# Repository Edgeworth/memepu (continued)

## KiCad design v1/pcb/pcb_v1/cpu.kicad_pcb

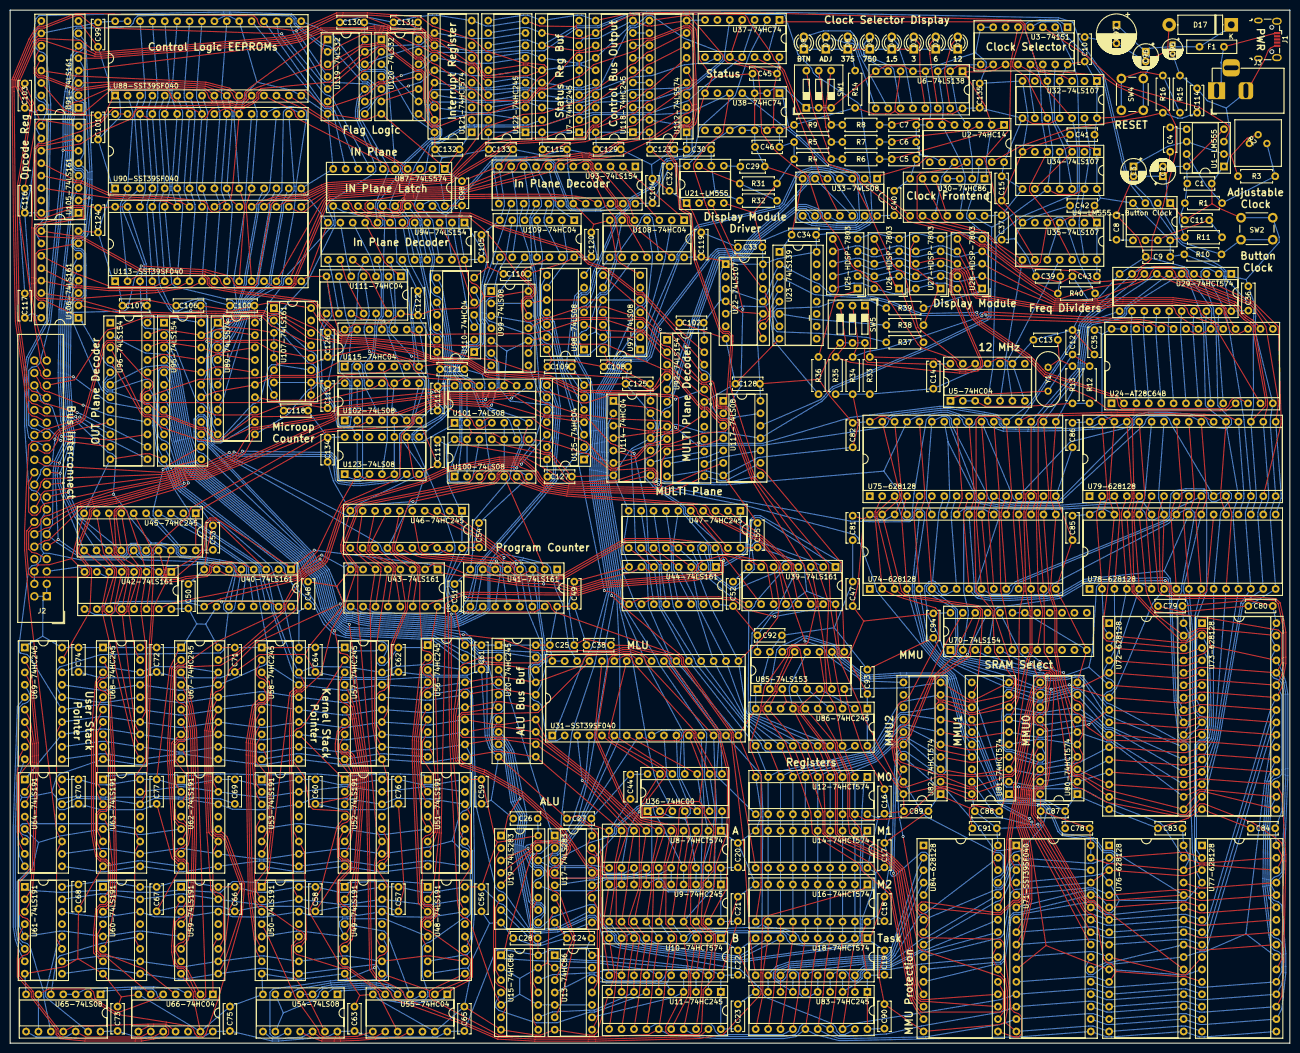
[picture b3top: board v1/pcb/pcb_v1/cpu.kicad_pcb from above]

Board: 2 copper layers, 262.0 x 211.5 mm, 299 parts (0 on the bottom side), 513 nets.

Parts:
C1, C5, C6, C7, C9, C10, C11, C14, C15, C16, C17, C18, C19, C20, C21, C22, C23, C24, C25, C26, C27, C28, C32, C33, C34, C35, C36, C37, C38, C40, C41, C42, C43, C44, C45, C46, C47, C48, C49, C50, C51, C52, C53, C54, C55, C56, C57, C58, C59, C60, C61, C62, C63, C64, C65, C66, C67, C68, C69, C70, C71, C72, C73, C74, C75, C76, C77, C78, C79, C80, C81, C82, C83, C84, C85, C86, C87, C88, C89, C90, C91, C92, C93, C94, C98, C99, C100, C101, C102, C103, C104, C105, C106, C107, C108, C109, C110, C111, C112, C113, C114, C115, C116, C117, C118, C119, C120, C121, C122, C123, C124, C125, C126, C127, C128, C129, C130, C131, C132, C133, C134, C135: 0.1uF; C_Disc_D6.0mm_W2.5mm_P5.00mm
C2, C3: 1uF; CP_Radial_D5.0mm_P2.00mm
C4, C8, C29: 10nF; C_Disc_D5.0mm_W2.5mm_P5.00mm
C12, C13: 27pF; C_Disc_D4.7mm_W2.5mm_P5.00mm
C30: 0.1nF; C_Disc_D6.0mm_W2.5mm_P5.00mm
C39: 1nF; C_Disc_D5.0mm_W2.5mm_P5.00mm
C95: 10uF; CP_Radial_D4.0mm_P2.00mm
C96: 100uF; CP_Radial_D5.0mm_P2.00mm
C97: 470uF; CP_Radial_D8.0mm_P3.80mm
D1, D2, D3, D4, D5, D6, D7, D8: LED; LED_D3.0mm
D17: 5.6V; D_5W_P12.70mm_Horizontal
F1: 0.65A; C_Disc_D10.0mm_W2.5mm_P5.00mm
J1: Conn_01x05; USB_Micro-B_Wuerth_629105150521
J2: Conn_02x20_Odd_Even; IDC-Header_2x20_P2.54mm_Vertical
J3: Conn_01x03; BarrelJack_Horizontal
R1, R13, R14: 1K; R_Axial_DIN0207_L6.3mm_D2.5mm_P7.62mm_Horizontal
R2: 1M; Akizuki-Denshi Potentiometer
R3, R31: 10K; R_Axial_DIN0207_L6.3mm_D2.5mm_P7.62mm_Horizontal
R4, R5, R9, R10, R15, R33, R34, R35: 100K; R_Axial_DIN0207_L6.3mm_D2.5mm_P7.62mm_Horizontal
R6, R7, R8, R11, R12, R16, R32, R40: 1M; R_Axial_DIN0207_L6.3mm_D2.5mm_P7.62mm_Horizontal
R36, R37, R38, R39: 100; R_Axial_DIN0207_L6.3mm_D2.5mm_P7.62mm_Horizontal
SW1: SW_DIP_x03 - Clock Source Select; SW_DIP_SPSTx03_Slide_9.78x9.8mm_W7.62mm_P2.54mm
SW2, SW4: SW_Push; SW_PUSH_6mm_H7.3mm
SW5: SW_DIP_x03; SW_DIP_SPSTx03_Slide_9.78x9.8mm_W7.62mm_P2.54mm
U1-LM555, U21-LM555: LM555; DIP-8_W7.62mm_Socket
U2-74HC14: 74HC14; DIP-14_W7.62mm_Socket
U3-74151: 74151; DIP-16_W7.62mm_Socket
U4-LM555 - Button Clock: LM555 - Button Clock; DIP-8_W7.62mm_Socket
U5-74HC04, U55-74HC04, U66-74HC04, U108-74HC04, U109-74HC04, U110-74HC04, U111-74HC04, U114-74HC04, U115-74HC04, U125-74HC04: 74HC04; DIP-14_W7.62mm_Socket
U6-74LS138: 74LS138; DIP-16_W7.62mm_Socket
U7-74HC245, U9-74HC245, U11-74HC245, U20-74HC245, U45-74HC245, U46-74HC245, U47-74HC245, U56-74HC245, U57-74HC245, U58-74HC245, U67-74HC245, U68-74HC245, U69-74HC245, U83-74HC245, U86-74HC245, U118-74HC245, U122-74HC245: 74HC245; DIP-20_W7.62mm_Socket
U8-74HCT574, U10-74HCT574, U12-74HCT574, U14-74HCT574, U16-74HCT574, U18-74HCT574, U29-74HCT574, U80-74HCT574, U81-74HCT574, U82-74HCT574, U121-74HCT574: 74HCT574; DIP-20_W7.62mm_Socket
U13-74HC86, U15-74HC86, U30-74HC86: 74HC86; DIP-14_W7.62mm_Socket
U17-74LS283, U19-74LS283: 74LS283; DIP-16_W7.62mm_Socket
U22-74LS107, U32-74LS107, U34-74LS107, U35-74LS107: 74LS107; DIP-14_W7.62mm_Socket
U23-74LS139: 74LS139; DIP-16_W7.62mm_Socket
U24-AT28C64B: AT28C64B; DIP-28_W15.24mm_Socket
U25-HDSP-7803, U26-HDSP-7803, U27-HDSP-7803, U28-HDSP-7803: HDSP-7803; HDSP-7801
U31-SST39SF040, U71-SST39SF040, U88-SST39SF040, U90-SST39SF040, U113-SST39SF040: SST39SF040; DIP-32_W15.24mm_Socket
U33-74LS08, U54-74LS08, U65-74LS08, U97-74LS08, U98-74LS08, U99-74LS08, U100-74LS08, U101-74LS08, U102-74LS08, U117-74LS08, U123-74LS08: 74LS08; DIP-14_W7.62mm_Socket
U36-74HC00: 74HC00; DIP-14_W7.62mm_Socket
U37-74HC74, U38-74HC74: 74HC74; DIP-14_W7.62mm_Socket
U39-74LS161, U40-74LS161, U41-74LS161, U42-74LS161, U43-74LS161, U44-74LS161, U91-74LS161, U105-74LS161, U106-74LS161, U107-74LS161: 74LS161; DIP-16_W7.62mm_Socket
U48-74LS191, U49-74LS191, U50-74LS191, U51-74LS191, U52-74LS191, U53-74LS191, U59-74LS191, U60-74LS191, U61-74LS191, U62-74LS191, U63-74LS191, U64-74LS191: 74LS191; DIP-16_W7.62mm_Socket
U70-74LS154, U92-74LS154, U93-74LS154, U94-74LS154, U95-74LS154, U96-74LS154: 74LS154; DIP-24_W7.62mm_Socket
U72-628128, U73-628128, U74-628128, U75-628128, U76-628128, U77-628128, U78-628128, U79-628128, U84-628128: 628128; DIP-32_W15.24mm_Socket
U85-74LS153: 74LS153; DIP-16_W7.62mm_Socket
U87-74LS574, U89-74LS574, U112-74LS574: 74LS574; DIP-20_W7.62mm_Socket
U119-74LS32, U120-74LS32: 74LS32; DIP-14_W7.62mm_Socket
Y1: 12MHz; Crystal_HC49-U_Vertical

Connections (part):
/A0: U8-74HCT574.19, U9-74HC245.2, U17-74LS283.5, U31-SST39SF040.12, U36-74HC00.1
/A1: U8-74HCT574.18, U9-74HC245.3, U17-74LS283.3, U31-SST39SF040.11, U36-74HC00.2
/A2: U8-74HCT574.17, U9-74HC245.4, U17-74LS283.14, U31-SST39SF040.10, U36-74HC00.4
/A3: U8-74HCT574.16, U9-74HC245.5, U17-74LS283.12, U31-SST39SF040.9, U36-74HC00.5
/A4: U8-74HCT574.15, U9-74HC245.6, U19-74LS283.5, U31-SST39SF040.8, U36-74HC00.9
/A5: U8-74HCT574.14, U9-74HC245.7, U19-74LS283.3, U31-SST39SF040.7, U36-74HC00.10
/A6: U8-74HCT574.13, U9-74HC245.8, U19-74LS283.14, U31-SST39SF040.6, U36-74HC00.12
/A7: U8-74HCT574.12, U9-74HC245.9, U19-74LS283.12, U31-SST39SF040.5, U36-74HC00.13
/ALU_FLAG_SET_CLK: U37-74HC74.3, U37-74HC74.11, U123-74LS08.8
/A_IN_CLK: U8-74HCT574.11, U97-74LS08.3
/B0: U10-74HCT574.19, U11-74HC245.2, U13-74HC86.1, U31-SST39SF040.27
/B1: U10-74HCT574.18, U11-74HC245.3, U13-74HC86.4, U31-SST39SF040.26
/B2: U10-74HCT574.17, U11-74HC245.4, U13-74HC86.9, U31-SST39SF040.23
/B3: U10-74HCT574.16, U11-74HC245.5, U13-74HC86.12, U31-SST39SF040.25
/B4: U10-74HCT574.15, U11-74HC245.6, U15-74HC86.1, U31-SST39SF040.4
/B5: U10-74HCT574.14, U11-74HC245.7, U15-74HC86.4, U31-SST39SF040.28
/B6: U10-74HCT574.13, U11-74HC245.8, U15-74HC86.9, U31-SST39SF040.29
/B7: U10-74HCT574.12, U11-74HC245.9, U15-74HC86.12, U31-SST39SF040.3
/BUS0: J2.9, U7-74HC245.18, U8-74HCT574.2, U9-74HC245.18, U10-74HCT574.2, U11-74HC245.18, U12-74HCT574.2, U12-74HCT574.19, U14-74HCT574.2, U14-74HCT574.19, U16-74HCT574.2, U16-74HCT574.19, U18-74HCT574.2, U20-74HC245.18, U29-74HCT574.2, U31-SST39SF040.13, U39-74LS161.3, U40-74LS161.3, U41-74LS161.3, U45-74HC245.18, U46-74HC245.18, U47-74HC245.18, U48-74LS191.15, U49-74LS191.15, U50-74LS191.15, U56-74HC245.18, U57-74HC245.18, U58-74HC245.18, U59-74LS191.15, U60-74LS191.15, U61-74LS191.15, U67-74HC245.18, U68-74HC245.18, U69-74HC245.18, U71-SST39SF040.13, U72-628128.13, U73-628128.13, U74-628128.13, U75-628128.13, U76-628128.13, U77-628128.13, U78-628128.13, U79-628128.13, U80-74HCT574.2, U81-74HCT574.2, U82-74HCT574.2, U83-74HC245.18, U86-74HC245.18, U91-74LS161.3, U105-74LS161.3, U118-74HC245.18, U122-74HC245.18
/BUS1: J2.11, U7-74HC245.17, U8-74HCT574.3, U9-74HC245.17, U10-74HCT574.3, U11-74HC245.17, U12-74HCT574.3, U12-74HCT574.18, U14-74HCT574.3, U14-74HCT574.18, U16-74HCT574.3, U16-74HCT574.18, U18-74HCT574.3, U20-74HC245.17, U29-74HCT574.3, U31-SST39SF040.14, U39-74LS161.4, U40-74LS161.4, U41-74LS161.4, U45-74HC245.17, U46-74HC245.17, U47-74HC245.17, U48-74LS191.1, U49-74LS191.1, U50-74LS191.1, U56-74HC245.17, U57-74HC245.17, U58-74HC245.17, U59-74LS191.1, U60-74LS191.1, U61-74LS191.1, U67-74HC245.17, U68-74HC245.17, U69-74HC245.17, U71-SST39SF040.14, U72-628128.14, U73-628128.14, U74-628128.14, U75-628128.14, U76-628128.14, U77-628128.14, U78-628128.14, U79-628128.14, U80-74HCT574.3, U81-74HCT574.3, U82-74HCT574.3, U83-74HC245.17, U86-74HC245.17, U91-74LS161.4, U105-74LS161.4, U118-74HC245.17, U122-74HC245.17
/BUS2: J2.13, U7-74HC245.16, U8-74HCT574.4, U9-74HC245.16, U10-74HCT574.4, U11-74HC245.16, U12-74HCT574.4, U12-74HCT574.17, U14-74HCT574.4, U14-74HCT574.17, U16-74HCT574.4, U16-74HCT574.17, U18-74HCT574.4, U20-74HC245.16, U29-74HCT574.4, U31-SST39SF040.15, U39-74LS161.5, U40-74LS161.5, U41-74LS161.5, U45-74HC245.16, U46-74HC245.16, U47-74HC245.16, U48-74LS191.10, U49-74LS191.10, U50-74LS191.10, U56-74HC245.16, U57-74HC245.16, U58-74HC245.16, U59-74LS191.10, U60-74LS191.10, U61-74LS191.10, U67-74HC245.16, U68-74HC245.16, U69-74HC245.16, U71-SST39SF040.15, U72-628128.15, U73-628128.15, U74-628128.15, U75-628128.15, U76-628128.15, U77-628128.15, U78-628128.15, U79-628128.15, U80-74HCT574.4, U81-74HCT574.4, U82-74HCT574.4, U83-74HC245.16, U86-74HC245.16, U91-74LS161.5, U105-74LS161.5, U118-74HC245.16, U122-74HC245.16
/BUS3: J2.15, U7-74HC245.15, U8-74HCT574.5, U9-74HC245.15, U10-74HCT574.5, U11-74HC245.15, U12-74HCT574.5, U12-74HCT574.16, U14-74HCT574.5, U14-74HCT574.16, U16-74HCT574.5, U16-74HCT574.16, U18-74HCT574.5, U20-74HC245.15, U29-74HCT574.5, U31-SST39SF040.17, U39-74LS161.6, U40-74LS161.6, U41-74LS161.6, U45-74HC245.15, U46-74HC245.15, U47-74HC245.15, U48-74LS191.9, U49-74LS191.9, U50-74LS191.9, U56-74HC245.15, U57-74HC245.15, U58-74HC245.15, U59-74LS191.9, U60-74LS191.9, U61-74LS191.9, U67-74HC245.15, U68-74HC245.15, U69-74HC245.15, U71-SST39SF040.17, U72-628128.17, U73-628128.17, U74-628128.17, U75-628128.17, U76-628128.17, U77-628128.17, U78-628128.17, U79-628128.17, U80-74HCT574.5, U81-74HCT574.5, U82-74HCT574.5, U83-74HC245.15, U86-74HC245.15, U91-74LS161.6, U105-74LS161.6, U118-74HC245.15, U122-74HC245.15
/BUS4: J2.17, U7-74HC245.14, U8-74HCT574.6, U9-74HC245.14, U10-74HCT574.6, U11-74HC245.14, U12-74HCT574.6, U12-74HCT574.15, U14-74HCT574.6, U14-74HCT574.15, U16-74HCT574.6, U16-74HCT574.15, U18-74HCT574.6, U20-74HC245.14, U29-74HCT574.6, U31-SST39SF040.18, U42-74LS161.3, U43-74LS161.3, U44-74LS161.3, U45-74HC245.14, U46-74HC245.14, U47-74HC245.14, U51-74LS191.15, U52-74LS191.15, U53-74LS191.15, U56-74HC245.14, U57-74HC245.14, U58-74HC245.14, U62-74LS191.15, U63-74LS191.15, U64-74LS191.15, U67-74HC245.14, U68-74HC245.14, U69-74HC245.14, U71-SST39SF040.18, U72-628128.18, U73-628128.18, U74-628128.18, U75-628128.18, U76-628128.18, U77-628128.18, U78-628128.18, U79-628128.18, U80-74HCT574.6, U81-74HCT574.6, U82-74HCT574.6, U83-74HC245.14, U86-74HC245.14, U106-74LS161.3, U118-74HC245.14, U122-74HC245.14
/BUS5: J2.19, U7-74HC245.13, U8-74HCT574.7, U9-74HC245.13, U10-74HCT574.7, U11-74HC245.13, U12-74HCT574.7, U12-74HCT574.14, U14-74HCT574.7, U14-74HCT574.14, U16-74HCT574.7, U16-74HCT574.14, U18-74HCT574.7, U20-74HC245.13, U29-74HCT574.7, U31-SST39SF040.19, U42-74LS161.4, U43-74LS161.4, U44-74LS161.4, U45-74HC245.13, U46-74HC245.13, U47-74HC245.13, U51-74LS191.1, U52-74LS191.1, U53-74LS191.1, U56-74HC245.13, U57-74HC245.13, U58-74HC245.13, U62-74LS191.1, U63-74LS191.1, U64-74LS191.1, U67-74HC245.13, U68-74HC245.13, U69-74HC245.13, U71-SST39SF040.19, U72-628128.19, U73-628128.19, U74-628128.19, U75-628128.19, U76-628128.19, U77-628128.19, U78-628128.19, U79-628128.19, U80-74HCT574.7, U81-74HCT574.7, U82-74HCT574.7, U83-74HC245.13, U86-74HC245.13, U106-74LS161.4, U118-74HC245.13, U122-74HC245.13
/BUS6: J2.21, U7-74HC245.12, U8-74HCT574.8, U9-74HC245.12, U10-74HCT574.8, U11-74HC245.12, U12-74HCT574.8, U12-74HCT574.13, U14-74HCT574.8, U14-74HCT574.13, U16-74HCT574.8, U16-74HCT574.13, U18-74HCT574.8, U20-74HC245.12, U29-74HCT574.8, U31-SST39SF040.20, U42-74LS161.5, U43-74LS161.5, U44-74LS161.5, U45-74HC245.12, U46-74HC245.12, U47-74HC245.12, U51-74LS191.10, U52-74LS191.10, U53-74LS191.10, U56-74HC245.12, U57-74HC245.12, U58-74HC245.12, U62-74LS191.10, U63-74LS191.10, U64-74LS191.10, U67-74HC245.12, U68-74HC245.12, U69-74HC245.12, U71-SST39SF040.20, U72-628128.20, U73-628128.20, U74-628128.20, U75-628128.20, U76-628128.20, U77-628128.20, U78-628128.20, U79-628128.20, U80-74HCT574.8, U81-74HCT574.8, U82-74HCT574.8, U83-74HC245.12, U86-74HC245.12, U106-74LS161.5, U118-74HC245.12, U122-74HC245.12
/BUS7: J2.23, U7-74HC245.11, U8-74HCT574.9, U9-74HC245.11, U10-74HCT574.9, U11-74HC245.11, U12-74HCT574.9, U12-74HCT574.12, U14-74HCT574.9, U14-74HCT574.12, U16-74HCT574.9, U16-74HCT574.12, U18-74HCT574.9, U20-74HC245.11, U29-74HCT574.9, U31-SST39SF040.21, U42-74LS161.6, U43-74LS161.6, U44-74LS161.6, U45-74HC245.11, U46-74HC245.11, U47-74HC245.11, U51-74LS191.9, U52-74LS191.9, U53-74LS191.9, U56-74HC245.11, U57-74HC245.11, U58-74HC245.11, U62-74LS191.9, U63-74LS191.9, U64-74LS191.9, U67-74HC245.11, U68-74HC245.11, U69-74HC245.11, U71-SST39SF040.21, U72-628128.21, U73-628128.21, U74-628128.21, U75-628128.21, U76-628128.21, U77-628128.21, U78-628128.21, U79-628128.21, U80-74HCT574.9, U81-74HCT574.9, U82-74HCT574.9, U83-74HC245.11, U86-74HC245.11, U106-74LS161.6, U118-74HC245.11, U122-74HC245.11
/B_IN_CLK: U10-74HCT574.11, U97-74LS08.6
/CARRY: U19-74LS283.9, U37-74HC74.2
/CLK: J2.5, U5-74HC04.13, U33-74LS08.3, U39-74LS161.2, U40-74LS161.2, U41-74LS161.2, U42-74LS161.2, U43-74LS161.2, U44-74LS161.2, U48-74LS191.14, U49-74LS191.14, U50-74LS191.14, U51-74LS191.14, U52-74LS191.14, U53-74LS191.14, U59-74LS191.14, U60-74LS191.14, U61-74LS191.14, U62-74LS191.14, U63-74LS191.14, U64-74LS191.14, U91-74LS161.2, U97-74LS08.2, U97-74LS08.5, U97-74LS08.10, U97-74LS08.13, U98-74LS08.2, U98-74LS08.5, U98-74LS08.10, U98-74LS08.13, U99-74LS08.2, U99-74LS08.5, U99-74LS08.10, U99-74LS08.13, U100-74LS08.2, U100-74LS08.5, U100-74LS08.10, U100-74LS08.13, U101-74LS08.2, U101-74LS08.5, U101-74LS08.10, U101-74LS08.13, U102-74LS08.2, U102-74LS08.5, U102-74LS08.10, U102-74LS08.13, U105-74LS161.2, U106-74LS161.2, U107-74LS161.2, U123-74LS08.2, U123-74LS08.5, U123-74LS08.10, U123-74LS08.13
/Clock/1.5MHZ_CLK: U3-74151.15, U34-74LS107.3, U34-74LS107.9
/Clock/3MHZ_CLK: U3-74151.14, U32-74LS107.5, U34-74LS107.12
/Clock/6MHZ_CLK: U3-74151.13, U32-74LS107.3, U32-74LS107.9
/Clock/12MHZ_CLK: U3-74151.12, U5-74HC04.4, U32-74LS107.12
/Clock/375KHZ_CLK: U3-74151.2, U35-74LS107.3
/Clock/750KHZ_CLK: U3-74151.1, U34-74LS107.5, U35-74LS107.12
/Clock/AC_TR: C3.1, R2.2, R3.2, U1-LM555.2, U1-LM555.6
/Clock/ADJ_CLK: U1-LM555.3, U3-74151.3
/Clock/BTN_CLK: U3-74151.4, U4-LM555 - Button Clock.3
/Clock/PRE_CLK: U3-74151.5, U33-74LS08.1, U35-74LS107.9
/Clock/SEL0: U2-74HC14.2, U3-74151.11, U6-74LS138.1, U30-74HC86.1
/Clock/SEL1: U2-74HC14.4, U3-74151.10, U6-74LS138.2, U30-74HC86.2
/Clock/SEL2: U2-74HC14.6, U3-74151.9, U6-74LS138.3, U30-74HC86.12
/Control Logic/ALU_FLAG_SET_NCLK: U114-74HC04.8, U123-74LS08.9
/Control Logic/A_IN_NCLK: U97-74LS08.1, U108-74HC04.2
/Control Logic/B_IN_NCLK: U97-74LS08.4, U108-74HC04.4
/Control Logic/CTRL0: U87-74LS574.2, U88-SST39SF040.13
/Control Logic/CTRL1: U87-74LS574.3, U88-SST39SF040.14
/Control Logic/CTRL2: U87-74LS574.4, U88-SST39SF040.15
/Control Logic/CTRL3: U87-74LS574.5, U88-SST39SF040.17
/Control Logic/CTRL4: U87-74LS574.6, U88-SST39SF040.18
/Control Logic/CTRL5: U87-74LS574.7, U88-SST39SF040.19
/Control Logic/CTRL6: U87-74LS574.8, U88-SST39SF040.20
/Control Logic/CTRL7: U87-74LS574.9, U88-SST39SF040.21
/Control Logic/CTRL8: U89-74LS574.2, U90-SST39SF040.13
/Control Logic/CTRL9: U89-74LS574.3, U90-SST39SF040.14
/Control Logic/CTRL10: U89-74LS574.4, U90-SST39SF040.15
/Control Logic/CTRL11: U89-74LS574.5, U90-SST39SF040.17
/Control Logic/CTRL12: U89-74LS574.6, U90-SST39SF040.18
/Control Logic/CTRL13: U89-74LS574.7, U90-SST39SF040.19
/Control Logic/CTRL14: U89-74LS574.8, U90-SST39SF040.20
/Control Logic/CTRL15: U89-74LS574.9, U90-SST39SF040.21
/Control Logic/CTRL16: U112-74LS574.2, U113-SST39SF040.13
/Control Logic/CTRL17: U112-74LS574.3, U113-SST39SF040.14
/Control Logic/CTRL18: U112-74LS574.4, U113-SST39SF040.15
/Control Logic/CTRL19: U112-74LS574.5, U113-SST39SF040.17
/Control Logic/CTRL20: U112-74LS574.6, U113-SST39SF040.18
/Control Logic/CTRL21: U112-74LS574.7, U113-SST39SF040.19
/Control Logic/CTRL22: U112-74LS574.8, U113-SST39SF040.20
/Control Logic/CTRL23: U112-74LS574.9, U113-SST39SF040.21
/Control Logic/CTRL_BUS1: U112-74LS574.18, U118-74HC245.3
/Control Logic/CTRL_BUS2: U112-74LS574.17, U118-74HC245.4
/Control Logic/CTRL_BUS3: U112-74LS574.16, U118-74HC245.5
/Control Logic/CTRL_BUS4: U112-74LS574.15, U118-74HC245.6
/Control Logic/CTRL_BUS5: U112-74LS574.14, U118-74HC245.7
/Control Logic/CTRL_BUS6: U112-74LS574.13, U118-74HC245.8
/Control Logic/CTRL_BUS7: U112-74LS574.12, U118-74HC245.9
/Control Logic/CTRL_IN0: U87-74LS574.19, U93-74LS154.23, U94-74LS154.23
/Control Logic/CTRL_IN1: U87-74LS574.18, U93-74LS154.22, U94-74LS154.22
/Control Logic/CTRL_IN2: U87-74LS574.17, U93-74LS154.21, U94-74LS154.21
/Control Logic/CTRL_IN3: U87-74LS574.16, U93-74LS154.20, U94-74LS154.20
/Control Logic/CTRL_IN4: U87-74LS574.15, U93-74LS154.18, U115-74HC04.11
/Control Logic/CTRL_MULTI0: U87-74LS574.14, U92-74LS154.23
/Control Logic/CTRL_MULTI1: U87-74LS574.13, U92-74LS154.22
/Control Logic/CTRL_MULTI2: U87-74LS574.12, U92-74LS154.21
/Control Logic/CTRL_MULTI3: U89-74LS574.14, U92-74LS154.20
/Control Logic/CTRL_OUT0: U89-74LS574.19, U95-74LS154.23, U96-74LS154.23
/Control Logic/CTRL_OUT1: U89-74LS574.18, U95-74LS154.22, U96-74LS154.22
/Control Logic/CTRL_OUT2: U89-74LS574.17, U95-74LS154.21, U96-74LS154.21
/Control Logic/CTRL_OUT3: U89-74LS574.16, U95-74LS154.20, U96-74LS154.20
/Control Logic/CTRL_OUT4: U89-74LS574.15, U95-74LS154.18, U115-74HC04.5
/Control Logic/DISP_IN_NCLK: U101-74LS08.1, U110-74HC04.10
/Control Logic/Flag Logic/INT_FLAG: U117-74LS08.1, U120-74LS32.8
/Control Logic/IN plane decoder/~S4: U94-74LS154.18, U115-74HC04.10
/Control Logic/INT0_IN_NCLK: U101-74LS08.9, U111-74HC04.2
/Control Logic/INT1_IN_NCLK: U101-74LS08.12, U111-74HC04.4
/Control Logic/INT2_IN_NCLK: U102-74LS08.1, U111-74HC04.6
/Control Logic/INT3_IN_NCLK: U102-74LS08.4, U111-74HC04.8
/Control Logic/INT4_IN_NCLK: U102-74LS08.9, U111-74HC04.10
/Control Logic/INT5_IN_NCLK: U102-74LS08.12, U111-74HC04.12
/Control Logic/INT6_IN_NCLK: U115-74HC04.2, U123-74LS08.1
/Control Logic/INT7_IN_NCLK: U115-74HC04.4, U123-74LS08.4
/Control Logic/INT_FLAG: U88-SST39SF040.2, U90-SST39SF040.2, U113-SST39SF040.2, U117-74LS08.3
/Control Logic/K0_IN_CLK: U99-74LS08.3, U125-74HC04.9
/Control Logic/K0_IN_NCLK: U99-74LS08.1, U109-74HC04.6
/Control Logic/K1_IN_CLK: U99-74LS08.6, U125-74HC04.11
/Control Logic/K1_IN_NCLK: U99-74LS08.4, U109-74HC04.8
/Control Logic/K2_IN_CLK: U99-74LS08.8, U125-74HC04.13
/Control Logic/K2_IN_NCLK: U99-74LS08.9, U109-74HC04.10
/Control Logic/M0_IN_NCLK: U97-74LS08.9, U108-74HC04.6
/Control Logic/M1_IN_NCLK: U97-74LS08.12, U108-74HC04.8
/Control Logic/M2_IN_NCLK: U98-74LS08.1, U108-74HC04.10
/Control Logic/MICROOP0: U88-SST39SF040.4, U90-SST39SF040.4, U107-74LS161.14, U113-SST39SF040.4
/Control Logic/MICROOP1: U88-SST39SF040.28, U90-SST39SF040.28, U107-74LS161.13, U113-SST39SF040.28
/Control Logic/MICROOP2: U88-SST39SF040.29, U90-SST39SF040.29, U107-74LS161.12, U113-SST39SF040.29
/Control Logic/MICROOP3: U88-SST39SF040.3, U90-SST39SF040.3, U107-74LS161.11, U113-SST39SF040.3
/Control Logic/MMU0_IN_NCLK: U99-74LS08.12, U109-74HC04.12
/Control Logic/MMU1_IN_NCLK: U100-74LS08.1, U110-74HC04.2
/Control Logic/MMU2_IN_NCLK: U100-74LS08.4, U110-74HC04.4
/Control Logic/MMU_CONTROL_IN_NCLK: U100-74LS08.12, U110-74HC04.8
/Control Logic/MMU_FAULT_FLAG: U88-SST39SF040.30, U90-SST39SF040.30, U113-SST39SF040.30, U120-74LS32.11
/Control Logic/MMU_IN_NCLK: U100-74LS08.9, U110-74HC04.6
/Control Logic/OP0: U88-SST39SF040.12, U90-SST39SF040.12, U91-74LS161.14, U113-SST39SF040.12
/Control Logic/OP1: U88-SST39SF040.11, U90-SST39SF040.11, U91-74LS161.13, U113-SST39SF040.11
/Control Logic/OP2: U88-SST39SF040.10, U90-SST39SF040.10, U91-74LS161.12, U113-SST39SF040.10
/Control Logic/OP3: U88-SST39SF040.9, U90-SST39SF040.9, U91-74LS161.11, U113-SST39SF040.9
/Control Logic/OP4: U88-SST39SF040.8, U90-SST39SF040.8, U106-74LS161.14, U113-SST39SF040.8
/Control Logic/OP5: U88-SST39SF040.7, U90-SST39SF040.7, U106-74LS161.13, U113-SST39SF040.7
/Control Logic/OP6: U88-SST39SF040.6, U90-SST39SF040.6, U106-74LS161.12, U113-SST39SF040.6
/Control Logic/OP7: U88-SST39SF040.5, U90-SST39SF040.5, U106-74LS161.11, U113-SST39SF040.5
/Control Logic/OP8: U88-SST39SF040.27, U90-SST39SF040.27, U105-74LS161.14, U113-SST39SF040.27
/Control Logic/OP9: U88-SST39SF040.26, U90-SST39SF040.26, U105-74LS161.13, U113-SST39SF040.26
/Control Logic/OP10: U88-SST39SF040.23, U90-SST39SF040.23, U105-74LS161.12, U113-SST39SF040.23
/Control Logic/OP11: U88-SST39SF040.25, U90-SST39SF040.25, U105-74LS161.11, U113-SST39SF040.25
/Control Logic/OPCODE0_INC_NCLK: U91-74LS161.7, U106-74LS161.7, U114-74HC04.4
/Control Logic/OPCODE1_INC_NCLK: U105-74LS161.7, U114-74HC04.6
/Control Logic/OUT plane decoder/~S4: U96-74LS154.18, U115-74HC04.6
/Control Logic/S0_IN_CLK: U98-74LS08.6, U125-74HC04.1
/Control Logic/S0_IN_NCLK: U98-74LS08.4, U108-74HC04.12
/Control Logic/S1_IN_CLK: U98-74LS08.8, U125-74HC04.3
/Control Logic/S1_IN_NCLK: U98-74LS08.9, U109-74HC04.2
/Control Logic/S2_IN_CLK: U98-74LS08.11, U125-74HC04.5
/Control Logic/S2_IN_NCLK: U98-74LS08.12, U109-74HC04.4
/Control Logic/TASK_IN_NCLK: U101-74LS08.4, U110-74HC04.12
/Control Logic/~ALU_FLAG_SET_NCLK: U92-74LS154.15, U114-74HC04.9
/Control Logic/~A_IN_NCLK: U93-74LS154.2, U108-74HC04.1
/Control Logic/~B_IN_NCLK: U93-74LS154.3, U108-74HC04.3
/Control Logic/~CTRLLOGIC_OUT_NCLK: U96-74LS154.7, U118-74HC245.19
/Control Logic/~DISP_IN_NCLK: U94-74LS154.5, U110-74HC04.11
/Control Logic/~INT0_IN_NCLK: U94-74LS154.9, U111-74HC04.1
/Control Logic/~INT1_IN_NCLK: U94-74LS154.10, U111-74HC04.3
/Control Logic/~INT2_IN_NCLK: U94-74LS154.11, U111-74HC04.5
/Control Logic/~INT3_IN_NCLK: U94-74LS154.13, U111-74HC04.9
/Control Logic/~INT4_IN_NCLK: U94-74LS154.14, U111-74HC04.11
/Control Logic/~INT5_IN_NCLK: U94-74LS154.15, U111-74HC04.13
/Control Logic/~INT6_IN_NCLK: U94-74LS154.16, U115-74HC04.1
/Control Logic/~INT7_IN_NCLK: U94-74LS154.17, U115-74HC04.3
/Control Logic/~K0_IN_NCLK: U93-74LS154.10, U109-74HC04.5
/Control Logic/~K1_IN_NCLK: U93-74LS154.11, U109-74HC04.9
/Control Logic/~K2_IN_NCLK: U93-74LS154.13, U109-74HC04.11
/Control Logic/~KSP_DEC_NCLK: U92-74LS154.14, U117-74LS08.10
/Control Logic/~M0_IN_NCLK: U93-74LS154.4, U108-74HC04.5
/Control Logic/~M1_IN_NCLK: U93-74LS154.5, U108-74HC04.9
/Control Logic/~M2_IN_NCLK: U93-74LS154.6, U108-74HC04.11
/Control Logic/~MMU0_IN_NCLK: U93-74LS154.17, U109-74HC04.13
/Control Logic/~MMU1_IN_NCLK: U94-74LS154.1, U110-74HC04.1
/Control Logic/~MMU2_IN_NCLK: U94-74LS154.2, U110-74HC04.3
/Control Logic/~MMU_CONTROL_IN_NCLK: U94-74LS154.4, U110-74HC04.9
/Control Logic/~MMU_IN_NCLK: U94-74LS154.3, U110-74HC04.5
/Control Logic/~OPCODE0_INC_NCLK: U92-74LS154.8, U114-74HC04.3
/Control Logic/~OPCODE0_IN_NCLK: U91-74LS161.9, U94-74LS154.7, U106-74LS161.9
/Control Logic/~OPCODE1_INC_NCLK: U92-74LS154.9, U114-74HC04.5
/Control Logic/~OPCODE1_IN_NCLK: U94-74LS154.8, U105-74LS161.9
/Control Logic/~PC_INC_NCLK: U92-74LS154.7, U114-74HC04.1
/Control Logic/~RESET_UOP_COUNT_NCLK: U92-74LS154.4, U107-74LS161.1
/Control Logic/~S0_IN_NCLK: U93-74LS154.7, U108-74HC04.13
/Control Logic/~S1_IN_NCLK: U93-74LS154.8, U109-74HC04.1
/Control Logic/~S2_IN_NCLK: U93-74LS154.9, U109-74HC04.3
/Control Logic/~SP_DEC_NCLK: U92-74LS154.11, U117-74LS08.5
/Control Logic/~SUB_NCLK: U92-74LS154.2, U115-74HC04.9
/Control Logic/~TASK_IN_NCLK: U94-74LS154.6, U110-74HC04.13
/DISP_IN_CLK: U29-74HCT574.11, U101-74LS08.3
/Display/C0: U22-74LS107.3, U22-74LS107.8, U22-74LS107.11, U23-74LS139.2, U24-AT28C64B.25
/Display/C1: U22-74LS107.5, U23-74LS139.3, U24-AT28C64B.24
/Display/DISP_CLK: U21-LM555.3, U22-74LS107.9, U22-74LS107.12
/Display/L0: R36.1, U25-HDSP-7803.1, U25-HDSP-7803.6
/Display/L1: R37.1, U26-HDSP-7803.1, U26-HDSP-7803.6
/Display/L2: R38.1, U27-HDSP-7803.1, U27-HDSP-7803.6
/Display/L3: R39.1, U28-HDSP-7803.1, U28-HDSP-7803.6
/Display/O0: U24-AT28C64B.11, U25-HDSP-7803.10, U26-HDSP-7803.10, U27-HDSP-7803.10, U28-HDSP-7803.10
/Display/O1: U24-AT28C64B.12, U25-HDSP-7803.9, U26-HDSP-7803.9, U27-HDSP-7803.9, U28-HDSP-7803.9
/Display/O2: U24-AT28C64B.13, U25-HDSP-7803.8, U26-HDSP-7803.8, U27-HDSP-7803.8, U28-HDSP-7803.8
/Display/O3: U24-AT28C64B.15, U25-HDSP-7803.5, U26-HDSP-7803.5, U27-HDSP-7803.5, U28-HDSP-7803.5
/Display/O4: U24-AT28C64B.16, U25-HDSP-7803.4, U26-HDSP-7803.4, U27-HDSP-7803.4, U28-HDSP-7803.4
/Display/O5: U24-AT28C64B.17, U25-HDSP-7803.2, U26-HDSP-7803.2, U27-HDSP-7803.2, U28-HDSP-7803.2
/Display/O6: U24-AT28C64B.18, U25-HDSP-7803.3, U26-HDSP-7803.3, U27-HDSP-7803.3, U28-HDSP-7803.3
/Display/O7: U24-AT28C64B.19, U25-HDSP-7803.7, U26-HDSP-7803.7, U27-HDSP-7803.7, U28-HDSP-7803.7
/Display/TR: C30.1, R32.2, U21-LM555.2, U21-LM555.6
/Display/sheet5B043D48/O0: U24-AT28C64B.10, U29-74HCT574.19
/Display/sheet5B043D48/O1: U24-AT28C64B.9, U29-74HCT574.18
/Display/sheet5B043D48/O2: U24-AT28C64B.8, U29-74HCT574.17
/Display/sheet5B043D48/O3: U24-AT28C64B.7, U29-74HCT574.16
/Display/sheet5B043D48/O4: U24-AT28C64B.6, U29-74HCT574.15
/Display/sheet5B043D48/O5: U24-AT28C64B.5, U29-74HCT574.14
/Display/sheet5B043D48/O6: U24-AT28C64B.4, U29-74HCT574.13
/Display/sheet5B043D48/O7: U24-AT28C64B.3, U29-74HCT574.12
/INT0_IN_CLK: J2.10, U101-74LS08.8
/INT0_LATCH: J2.25, U119-74LS32.1, U121-74HCT574.19, U122-74HC245.2
/INT1_IN_CLK: J2.12, U101-74LS08.11
/INT1_LATCH: J2.27, U119-74LS32.2, U121-74HCT574.18, U122-74HC245.3
/INT2_IN_CLK: J2.14, U102-74LS08.3
/INT2_LATCH: J2.29, U119-74LS32.4, U121-74HCT574.17, U122-74HC245.4
/INT3_IN_CLK: J2.16, U102-74LS08.6
/INT3_LATCH: J2.31, U119-74LS32.5, U121-74HCT574.16, U122-74HC245.5
/INT4_IN_CLK: J2.18, U102-74LS08.8
/INT4_LATCH: J2.33, U119-74LS32.9, U121-74HCT574.15, U122-74HC245.6
/INT5_IN_CLK: J2.20, U102-74LS08.11
/INT5_LATCH: J2.35, U119-74LS32.10, U121-74HCT574.14, U122-74HC245.7
/INT6_IN_CLK: J2.22, U123-74LS08.3
/INT6_LATCH: J2.37, U119-74LS32.12, U121-74HCT574.13, U122-74HC245.8
/INT7_IN_CLK: J2.24, U123-74LS08.6
/INT7_LATCH: J2.39, U119-74LS32.13, U121-74HCT574.12, U122-74HC245.9
/INTERRUPT_ENABLE_FLAG: U7-74HC245.2, U38-74HC74.5, U117-74LS08.2
/Kernel Stack Register/CARRY0: U48-74LS191.12, U54-74LS08.1, U55-74HC04.1
/Kernel Stack Register/CARRY1: U51-74LS191.12, U54-74LS08.2
/Kernel Stack Register/CARRY2: U49-74LS191.12, U54-74LS08.5
/Kernel Stack Register/CARRY3: U52-74LS191.12, U54-74LS08.10
/Kernel Stack Register/CARRY4: U50-74LS191.12, U54-74LS08.13
/Kernel Stack Register/O0: U48-74LS191.3, U56-74HC245.2
/Kernel Stack Register/O1: U48-74LS191.2, U56-74HC245.3
/Kernel Stack Register/O2: U48-74LS191.6, U56-74HC245.4
/Kernel Stack Register/O3: U48-74LS191.7, U56-74HC245.5
/Kernel Stack Register/O4: U51-74LS191.3, U56-74HC245.6
/Kernel Stack Register/O5: U51-74LS191.2, U56-74HC245.7
/Kernel Stack Register/O6: U51-74LS191.6, U56-74HC245.8
/Kernel Stack Register/O7: U51-74LS191.7, U56-74HC245.9
/Kernel Stack Register/O8: U49-74LS191.3, U57-74HC245.2
/Kernel Stack Register/O9: U49-74LS191.2, U57-74HC245.3
/Kernel Stack Register/O10: U49-74LS191.6, U57-74HC245.4
/Kernel Stack Register/O11: U49-74LS191.7, U57-74HC245.5
/Kernel Stack Register/O12: U52-74LS191.3, U57-74HC245.6
/Kernel Stack Register/O13: U52-74LS191.2, U57-74HC245.7
/Kernel Stack Register/O14: U52-74LS191.6, U57-74HC245.8
/Kernel Stack Register/O15: U52-74LS191.7, U57-74HC245.9
/Kernel Stack Register/O16: U50-74LS191.3, U58-74HC245.2
/Kernel Stack Register/O17: U50-74LS191.2, U58-74HC245.3
/Kernel Stack Register/O18: U50-74LS191.6, U58-74HC245.4
/Kernel Stack Register/O19: U50-74LS191.7, U58-74HC245.5
/Kernel Stack Register/O20: U53-74LS191.3, U58-74HC245.6
/Kernel Stack Register/O21: U53-74LS191.2, U58-74HC245.7
/Kernel Stack Register/O22: U53-74LS191.6, U58-74HC245.8
/Kernel Stack Register/O23: U53-74LS191.7, U58-74HC245.9
/Kernel Stack Register/~ENABLE1: U51-74LS191.4, U55-74HC04.2
/Kernel Stack Register/~ENABLE2: U49-74LS191.4, U55-74HC04.4
/Kernel Stack Register/~ENABLE3: U52-74LS191.4, U55-74HC04.6
/Kernel Stack Register/~ENABLE4: U50-74LS191.4, U55-74HC04.8
/Kernel Stack Register/~ENABLE5: U53-74LS191.4, U55-74HC04.10
/M0_IN_CLK: U12-74HCT574.11, U97-74LS08.8
/M1_IN_CLK: U14-74HCT574.11, U97-74LS08.11
/M2_IN_CLK: U16-74HCT574.11, U98-74LS08.3
/MLU_SEL0: U31-SST39SF040.2, U89-74LS574.13
/MLU_SEL1: U31-SST39SF040.30, U89-74LS574.12
/MLU_SEL2: U31-SST39SF040.1, U112-74LS574.19, U118-74HC245.2
/MMU0_IN_CLK: U80-74HCT574.11, U99-74LS08.11
/MMU1_IN_CLK: U81-74HCT574.11, U100-74LS08.3
/MMU2_IN_CLK: U82-74HCT574.11, U100-74LS08.6
/MMU/M0: U71-SST39SF040.12, U72-628128.12, U73-628128.12, U74-628128.12, U75-628128.12, U76-628128.12, U77-628128.12, U78-628128.12, U79-628128.12, U80-74HCT574.19
/MMU/M1: U71-SST39SF040.11, U72-628128.11, U73-628128.11, U74-628128.11, U75-628128.11, U76-628128.11, U77-628128.11, U78-628128.11, U79-628128.11, U80-74HCT574.18
/MMU/M2: U71-SST39SF040.10, U72-628128.10, U73-628128.10, U74-628128.10, U75-628128.10, U76-628128.10, U77-628128.10, U78-628128.10, U79-628128.10, U80-74HCT574.17
/MMU/M3: U71-SST39SF040.9, U72-628128.9, U73-628128.9, U74-628128.9, U75-628128.9, U76-628128.9, U77-628128.9, U78-628128.9, U79-628128.9, U80-74HCT574.16
/MMU/M4: U71-SST39SF040.8, U72-628128.8, U73-628128.8, U74-628128.8, U75-628128.8, U76-628128.8, U77-628128.8, U78-628128.8, U79-628128.8, U80-74HCT574.15
/MMU/M5: U71-SST39SF040.7, U72-628128.7, U73-628128.7, U74-628128.7, U75-628128.7, U76-628128.7, U77-628128.7, U78-628128.7, U79-628128.7, U80-74HCT574.14
/MMU/M6: U71-SST39SF040.6, U72-628128.6, U73-628128.6, U74-628128.6, U75-628128.6, U76-628128.6, U77-628128.6, U78-628128.6, U79-628128.6, U80-74HCT574.13
/MMU/M7: U71-SST39SF040.5, U72-628128.5, U73-628128.5, U74-628128.5, U75-628128.5, U76-628128.5, U77-628128.5, U78-628128.5, U79-628128.5, U80-74HCT574.12
/MMU/M8: U71-SST39SF040.27, U72-628128.27, U73-628128.27, U74-628128.27, U75-628128.27, U76-628128.27, U77-628128.27, U78-628128.27, U79-628128.27, U81-74HCT574.19
/MMU/M9: U71-SST39SF040.26, U72-628128.26, U73-628128.26, U74-628128.26, U75-628128.26, U76-628128.26, U77-628128.26, U78-628128.26, U79-628128.26, U81-74HCT574.18
/MMU/M10: U71-SST39SF040.23, U72-628128.23, U73-628128.23, U74-628128.23, U75-628128.23, U76-628128.23, U77-628128.23, U78-628128.23, U79-628128.23, U81-74HCT574.17, U85-74LS153.14
/MMU/M11: U71-SST39SF040.25, U72-628128.25, U73-628128.25, U74-628128.25, U75-628128.25, U76-628128.25, U77-628128.25, U78-628128.25, U79-628128.25, U81-74HCT574.16, U85-74LS153.2
/MMU/M12: U71-SST39SF040.4, U72-628128.4, U73-628128.4, U74-628128.4, U75-628128.4, U76-628128.4, U77-628128.4, U78-628128.4, U79-628128.4, U81-74HCT574.15, U84-628128.12
/MMU/M13: U71-SST39SF040.28, U72-628128.28, U73-628128.28, U74-628128.28, U75-628128.28, U76-628128.28, U77-628128.28, U78-628128.28, U79-628128.28, U81-74HCT574.14, U84-628128.11
/MMU/M14: U71-SST39SF040.29, U72-628128.3, U73-628128.3, U74-628128.3, U75-628128.3, U76-628128.3, U77-628128.3, U78-628128.3, U79-628128.3, U81-74HCT574.13, U84-628128.10
/MMU/M15: U71-SST39SF040.3, U72-628128.31, U73-628128.31, U74-628128.31, U75-628128.31, U76-628128.31, U77-628128.31, U78-628128.31, U79-628128.31, U81-74HCT574.12, U84-628128.9
/MMU/M16: U71-SST39SF040.2, U72-628128.2, U73-628128.2, U74-628128.2, U75-628128.2, U76-628128.2, U77-628128.2, U78-628128.2, U79-628128.2, U82-74HCT574.19, U84-628128.8
/MMU/M17: U70-74LS154.23, U71-SST39SF040.30, U82-74HCT574.18, U84-628128.7
/MMU/M18: U70-74LS154.22, U71-SST39SF040.1, U82-74HCT574.17, U84-628128.6
/MMU/M19: U70-74LS154.21, U82-74HCT574.16, U84-628128.5
/MMU/M20: U70-74LS154.20, U71-SST39SF040.24, U82-74HCT574.15, U84-628128.27
/MMU/READ0: U84-628128.13, U85-74LS153.6, U86-74HC245.2
/MMU/READ1: U84-628128.15, U85-74LS153.5, U86-74HC245.4
/MMU/READ2: U84-628128.18, U85-74LS153.4, U86-74HC245.6
/MMU/READ3: U84-628128.20, U85-74LS153.3, U86-74HC245.8
/MMU/WRITE0: U84-628128.14, U85-74LS153.10, U86-74HC245.3
/MMU/WRITE1: U84-628128.17, U85-74LS153.11, U86-74HC245.5
/MMU/WRITE2: U84-628128.19, U85-74LS153.12, U86-74HC245.7
/MMU/WRITE3: U84-628128.21, U85-74LS153.13, U86-74HC245.9
/MMU/~SEL0: U70-74LS154.1, U72-628128.22
/MMU/~SEL1: U70-74LS154.2, U74-628128.22
/MMU/~SEL2: U70-74LS154.3, U76-628128.22
/MMU/~SEL3: U70-74LS154.4, U78-628128.22
/MMU/~SEL4: U70-74LS154.5, U73-628128.22
/MMU/~SEL5: U70-74LS154.6, U75-628128.22
/MMU/~SEL6: U70-74LS154.7, U77-628128.22
/MMU/~SEL7: U70-74LS154.8, U79-628128.22
/MMU_CONTROL_IN_CLK: U84-628128.29, U100-74LS08.11
/MMU_IN_CLK: U72-628128.29, U73-628128.29, U74-628128.29, U75-628128.29, U76-628128.29, U77-628128.29, U78-628128.29, U79-628128.29, U100-74LS08.8
/MMU_READ_FAULT: U85-74LS153.7, U120-74LS32.12
/MMU_WRITE_FAULT: U85-74LS153.9, U120-74LS32.13
/PC_INC_NCLK: U39-74LS161.7, U40-74LS161.7, U41-74LS161.7, U42-74LS161.7, U43-74LS161.7, U44-74LS161.7, U114-74HC04.2
/Program Counter/CARRY0: U40-74LS161.15, U42-74LS161.10
/Program Counter/CARRY1: U41-74LS161.10, U42-74LS161.15
/Program Counter/CARRY2: U41-74LS161.15, U43-74LS161.10
/Program Counter/CARRY3: U39-74LS161.10, U43-74LS161.15
/Program Counter/CARRY4: U39-74LS161.15, U44-74LS161.10
/Program Counter/PC0: U40-74LS161.14, U45-74HC245.2
/Program Counter/PC1: U40-74LS161.13, U45-74HC245.3
/Program Counter/PC2: U40-74LS161.12, U45-74HC245.4
/Program Counter/PC3: U40-74LS161.11, U45-74HC245.5
/Program Counter/PC4: U42-74LS161.14, U45-74HC245.6
/Program Counter/PC5: U42-74LS161.13, U45-74HC245.7
/Program Counter/PC6: U42-74LS161.12, U45-74HC245.8
/Program Counter/PC7: U42-74LS161.11, U45-74HC245.9
/Program Counter/PC8: U41-74LS161.14, U46-74HC245.2
/Program Counter/PC9: U41-74LS161.13, U46-74HC245.3
/Program Counter/PC10: U41-74LS161.12, U46-74HC245.4
/Program Counter/PC11: U41-74LS161.11, U46-74HC245.5
/Program Counter/PC12: U43-74LS161.14, U46-74HC245.6
/Program Counter/PC13: U43-74LS161.13, U46-74HC245.7
/Program Counter/PC14: U43-74LS161.12, U46-74HC245.8
/Program Counter/PC15: U43-74LS161.11, U46-74HC245.9
/Program Counter/PC16: U39-74LS161.14, U47-74HC245.2
/Program Counter/PC17: U39-74LS161.13, U47-74HC245.3
/Program Counter/PC18: U39-74LS161.12, U47-74HC245.4
/Program Counter/PC19: U39-74LS161.11, U47-74HC245.5
/Program Counter/PC20: U44-74LS161.14, U47-74HC245.6
/Program Counter/PC21: U44-74LS161.13, U47-74HC245.7
/Program Counter/PC22: U44-74LS161.12, U47-74HC245.8
/Program Counter/PC23: U44-74LS161.11, U47-74HC245.9
/SUB_NCLK: U13-74HC86.2, U13-74HC86.5, U13-74HC86.10, U13-74HC86.13, U15-74HC86.2, U15-74HC86.5, U15-74HC86.10, U15-74HC86.13, U17-74LS283.7, U115-74HC04.8
/Status/Control Register/CARRY_FLAG: U7-74HC245.3, U37-74HC74.5
/Status/Control Register/ZERO_FLAG: U7-74HC245.4, U37-74HC74.9
/TASK0: U18-74HCT574.19, U83-74HC245.2, U84-628128.26
/TASK1: U18-74HCT574.18, U83-74HC245.3, U84-628128.23
/TASK2: U18-74HCT574.17, U83-74HC245.4, U84-628128.25
/TASK3: U18-74HCT574.16, U83-74HC245.5, U84-628128.4
/TASK4: U18-74HCT574.15, U83-74HC245.6, U84-628128.28
/TASK5: U18-74HCT574.14, U83-74HC245.7, U84-628128.3
/TASK6: U18-74HCT574.13, U83-74HC245.8, U84-628128.31
/TASK7: U18-74HCT574.12, U83-74HC245.9, U84-628128.2
/TASK_IN_CLK: U18-74HCT574.11, U101-74LS08.6
/User Stack Register/CARRY0: U59-74LS191.12, U65-74LS08.1, U66-74HC04.1
/User Stack Register/CARRY1: U62-74LS191.12, U65-74LS08.2
/User Stack Register/CARRY2: U60-74LS191.12, U65-74LS08.5
/User Stack Register/CARRY3: U63-74LS191.12, U65-74LS08.10
/User Stack Register/CARRY4: U61-74LS191.12, U65-74LS08.13
/User Stack Register/O0: U59-74LS191.3, U67-74HC245.2
/User Stack Register/O1: U59-74LS191.2, U67-74HC245.3
/User Stack Register/O2: U59-74LS191.6, U67-74HC245.4
/User Stack Register/O3: U59-74LS191.7, U67-74HC245.5
/User Stack Register/O4: U62-74LS191.3, U67-74HC245.6
/User Stack Register/O5: U62-74LS191.2, U67-74HC245.7
/User Stack Register/O6: U62-74LS191.6, U67-74HC245.8
/User Stack Register/O7: U62-74LS191.7, U67-74HC245.9
/User Stack Register/O8: U60-74LS191.3, U68-74HC245.2
/User Stack Register/O9: U60-74LS191.2, U68-74HC245.3
/User Stack Register/O10: U60-74LS191.6, U68-74HC245.4
/User Stack Register/O11: U60-74LS191.7, U68-74HC245.5
/User Stack Register/O12: U63-74LS191.3, U68-74HC245.6
/User Stack Register/O13: U63-74LS191.2, U68-74HC245.7
/User Stack Register/O14: U63-74LS191.6, U68-74HC245.8
/User Stack Register/O15: U63-74LS191.7, U68-74HC245.9
/User Stack Register/O16: U61-74LS191.3, U69-74HC245.2
/User Stack Register/O17: U61-74LS191.2, U69-74HC245.3
/User Stack Register/O18: U61-74LS191.6, U69-74HC245.4
/User Stack Register/O19: U61-74LS191.7, U69-74HC245.5
/User Stack Register/O20: U64-74LS191.3, U69-74HC245.6
/User Stack Register/O21: U64-74LS191.2, U69-74HC245.7
/User Stack Register/O22: U64-74LS191.6, U69-74HC245.8
/User Stack Register/O23: U64-74LS191.7, U69-74HC245.9
/User Stack Register/~ENABLE1: U62-74LS191.4, U66-74HC04.2
/User Stack Register/~ENABLE2: U60-74LS191.4, U66-74HC04.4
/User Stack Register/~ENABLE3: U63-74LS191.4, U66-74HC04.6
/User Stack Register/~ENABLE4: U61-74LS191.4, U66-74HC04.8
/User Stack Register/~ENABLE5: U64-74LS191.4, U66-74HC04.10
/ZERO: U33-74LS08.11, U37-74HC74.12
/~A_OUT_NCLK: U9-74HC245.19, U95-74LS154.2
/~B_OUT_NCLK: U11-74HC245.19, U95-74LS154.3
/~CLK: J2.7, U5-74HC04.12, U87-74LS574.11, U89-74LS574.11, U112-74LS574.11
/~INT0_OUT_NCLK: J2.26, U96-74LS154.9
/~INT1_OUT_NCLK: J2.28, U96-74LS154.10
/~INT2_OUT_NCLK: J2.30, U96-74LS154.11
/~INT3_OUT_NCLK: J2.32, U96-74LS154.13
/~INT4_OUT_NCLK: J2.34, U96-74LS154.14
/~INT5_OUT_NCLK: J2.36, U96-74LS154.15
/~INT6_OUT_NCLK: J2.38, U96-74LS154.16
/~INT7_OUT_NCLK: J2.40, U96-74LS154.17
/~K0_IN_CLK: U48-74LS191.11, U51-74LS191.11, U125-74HC04.8
/~K0_OUT_NCLK: U56-74HC245.19, U95-74LS154.10
/~K1_IN_CLK: U49-74LS191.11, U52-74LS191.11, U125-74HC04.10
/~K1_OUT_NCLK: U57-74HC245.19, U95-74LS154.11
/~K2_IN_CLK: U50-74LS191.11, U53-74LS191.11, U125-74HC04.12
/~K2_OUT_NCLK: U58-74HC245.19, U95-74LS154.13
/~KSP_COUNT_NCLK: U48-74LS191.4, U117-74LS08.8
/~KSP_INC_NCLK: U48-74LS191.5, U49-74LS191.5, U50-74LS191.5, U51-74LS191.5, U52-74LS191.5, U53-74LS191.5, U92-74LS154.13, U117-74LS08.9
/~M0_OUT_NCLK: U12-74HCT574.1, U95-74LS154.4
/~M1_OUT_NCLK: U14-74HCT574.1, U95-74LS154.5
/~M2_OUT_NCLK: U16-74HCT574.1, U95-74LS154.6
/~MLU_OUT_NCLK: U31-SST39SF040.24, U96-74LS154.6
/~MMU_CONTROL_OUT_NCLK: U86-74HC245.19, U96-74LS154.4
/~MMU_OUT_NCLK: U71-SST39SF040.22, U72-628128.24, U73-628128.24, U74-628128.24, U75-628128.24, U76-628128.24, U77-628128.24, U78-628128.24, U79-628128.24, U96-74LS154.3
/~PC0_IN_NCLK: U40-74LS161.9, U42-74LS161.9, U93-74LS154.14
/~PC0_OUT_NCLK: U45-74HC245.19, U95-74LS154.14
/~PC1_IN_NCLK: U41-74LS161.9, U43-74LS161.9, U93-74LS154.15
/~PC1_OUT_NCLK: U46-74HC245.19, U95-74LS154.15
/~PC2_IN_NCLK: U39-74LS161.9, U44-74LS161.9, U93-74LS154.16
/~PC2_OUT_NCLK: U47-74HC245.19, U95-74LS154.16
/~RESET: U30-74HC86.13, U32-74LS107.10, U32-74LS107.13, U34-74LS107.10, U34-74LS107.13, U35-74LS107.13, U37-74HC74.1, U37-74HC74.13, U39-74LS161.1, U40-74LS161.1, U41-74LS161.1, U42-74LS161.1, U43-74LS161.1, U44-74LS161.1, U91-74LS161.1, U105-74LS161.1, U106-74LS161.1, U117-74LS08.11
/~RESET_NCLK: U92-74LS154.3, U117-74LS08.13
/~S0_IN_CLK: U59-74LS191.11, U62-74LS191.11, U125-74HC04.2
/~S0_OUT_NCLK: U67-74HC245.19, U95-74LS154.7
/~S1_IN_CLK: U60-74LS191.11, U63-74LS191.11, U125-74HC04.4
/~S1_OUT_NCLK: U68-74HC245.19, U95-74LS154.8
/~S2_IN_CLK: U61-74LS191.11, U64-74LS191.11, U125-74HC04.6
/~S2_OUT_NCLK: U69-74HC245.19, U95-74LS154.9
/~SET_INT_ENABLE_ASYNC: U38-74HC74.4, U92-74LS154.5
/~SP_COUNT_NCLK: U59-74LS191.4, U117-74LS08.6
/~SP_INC_NCLK: U59-74LS191.5, U60-74LS191.5, U61-74LS191.5, U62-74LS191.5, U63-74LS191.5, U64-74LS191.5, U92-74LS154.10, U117-74LS08.4
/~STATUS_OUT_NCLK: U7-74HC245.19, U95-74LS154.17
/~SUM_OUT_NCLK: U20-74HC245.19, U96-74LS154.2
/~TASK_OUT_NCLK: U83-74HC245.19, U96-74LS154.5
/~UNSET_INT_ENABLE_ASYNC: U38-74HC74.1, U92-74LS154.6
GND: C1.2, C2.1, C3.2, C4.2, C5.1, C6.1, C7.1, C8.2, C9.2, C10.2, C11.1, C12.2, C13.2, C14.2, C15.1, C16.2, C17.2, C18.2, C19.2, C20.2, C21.2, C22.2, C23.2, C24.1, C25.1, C26.2, C27.2, C28.2, C29.2, C30.2, C32.1, C33.2, C34.2, C35.1, C36.2, C37.1, C38.1, C39.2, C40.1, C41.1, C42.1, C43.1, C44.2, C45.1, C46.1, C47.1, C48.1, C49.1, C50.1, C51.1, C52.1, C53.2, C54.2, C55.2, C56.1, C57.1, C58.1, C59.1, C60.1, C61.1, C62.1, C63.1, C64.1, C65.1, C66.1, C67.1, C68.1, C69.1, C70.1, C71.1, C72.1, C73.1, C74.1, C75.1, C76.1, C77.1, C78.1, C79.1, C80.1, C81.1, C82.1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
unnamed: C4.1, U1-LM555.5
unnamed: C5.2, R6.1, U2-74HC14.1
unnamed: C6.2, R7.1, U2-74HC14.3
unnamed: C7.2, R8.1, U2-74HC14.5
unnamed: C8.1, U4-LM555 - Button Clock.5
unnamed: C11.2, R11.2, U4-LM555 - Button Clock.6, U4-LM555 - Button Clock.7
unnamed: C12.1, R12.2, U5-74HC04.1, Y1.1
unnamed: C13.1, R13.2, Y1.2
unnamed: C29.1, U21-LM555.5
unnamed: C39.1, R40.1, U2-74HC14.11
unnamed: C114.2, R16.1, U2-74HC14.13
unnamed: D1.1, D2.1, D3.1, D4.1, D5.1, D6.1, D7.1, D8.1, R14.2
unnamed: D1.2, U6-74LS138.15
unnamed: D2.2, U6-74LS138.14
unnamed: D3.2, U6-74LS138.13
unnamed: D4.2, U6-74LS138.12
unnamed: D5.2, U6-74LS138.11
unnamed: D6.2, U6-74LS138.10
unnamed: D7.2, U6-74LS138.9
unnamed: D8.2, U6-74LS138.7
unnamed: F1.1, J1.1, J3.1
unnamed: R1.2, R2.1, R3.1, U1-LM555.7
unnamed: R4.2, R6.2, SW1.6
unnamed: R5.2, R7.2, SW1.5
unnamed: R8.2, R9.2, SW1.4
unnamed: R10.1, SW2.2, U4-LM555 - Button Clock.2
unnamed: R12.1, R13.1, U5-74HC04.2, U5-74HC04.3
unnamed: R15.1, R16.2, SW4.1
unnamed: R31.2, R32.1, U21-LM555.7
unnamed: R33.1, SW5.1, U24-AT28C64B.21
unnamed: R34.1, SW5.2, U24-AT28C64B.23
unnamed: R35.1, SW5.3, U24-AT28C64B.2
unnamed: R36.2, U23-74LS139.4
unnamed: R37.2, U23-74LS139.5
unnamed: R38.2, U23-74LS139.6
unnamed: R39.2, U23-74LS139.7
unnamed: R40.2, U30-74HC86.9, U35-74LS107.5
unnamed: U2-74HC14.10, U30-74HC86.10
unnamed: U13-74HC86.3, U17-74LS283.6
unnamed: U13-74HC86.6, U17-74LS283.2
unnamed: U13-74HC86.8, U17-74LS283.15
unnamed: U13-74HC86.11, U17-74LS283.11
unnamed: U15-74HC86.3, U19-74LS283.6
unnamed: U15-74HC86.6, U19-74LS283.2
unnamed: U15-74HC86.8, U19-74LS283.15
unnamed: U15-74HC86.11, U19-74LS283.11
unnamed: U17-74LS283.1, U20-74HC245.3
unnamed: U17-74LS283.4, U20-74HC245.2
unnamed: U17-74LS283.9, U19-74LS283.7
unnamed: U17-74LS283.10, U20-74HC245.5
unnamed: U17-74LS283.13, U20-74HC245.4
unnamed: U19-74LS283.1, U20-74HC245.7
unnamed: U19-74LS283.4, U20-74HC245.6
unnamed: U19-74LS283.10, U20-74HC245.9
unnamed: U19-74LS283.13, U20-74HC245.8
unnamed: U30-74HC86.3, U30-74HC86.4
unnamed: U5-74HC04.5, U30-74HC86.6, U35-74LS107.8
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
